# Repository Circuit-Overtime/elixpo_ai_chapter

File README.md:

<div align="center">

# LixBlogs

### Write, collaborate, and publish beautifully.

A modern blogging platform with a rich block editor, AI writing assistant,<br />
real-time collaboration, and organizations — all on the edge.

<br />

[Website](https://blogs.elixpo.com) ·
[Discussions](https://github.com/orgs/elixpo/discussions) ·
[Elixpo](https://elixpo.com) ·
[Chapter](https://github.com/elixpo/elixpo_chapter)

</div>

<br />

<div align="center">

</div>

<br />

## About

LixBlogs (also called **Elixpo Blogs**) is an **open-source publishing
platform** designed for creators, developers, and teams. It gives you a
beautiful writing experience with powerful tools built right in — a rich block
editor, an AI writing assistant, real-time collaboration, and organizations —
all deployed on **Cloudflare's edge** and hosted at
[blogs.elixpo.com](https://blogs.elixpo.com).

It supports personal publishing, organization publications, and collaborative
editing. Availability, account requirements, and operated-service limits are
documented by the hosted service rather than promised by this README.

This is a monorepo: alongside the platform it ships **`@elixpo/lixeditor`** (the
editor on npm) and the **LixEditor** VS Code extension. It is part of the wider
Elixpo ecosystem.

<br />

<div align="center">

| | Feature | Description |
|:---:|:---|:---|
| :sparkles: | **AI Writing Assistant** | Press `Space` on an empty line — generate text, images, and get inline suggestions |
| :jigsaw: | **Rich Block Editor** | 20+ block types — code, math equations, diagrams, embeds, tables, and more |
| :busts_in_silhouette: | **Real-Time Collaboration** | Invite co-authors and edit together with live cursors and presence |
| :office: | **Organizations & Teams** | Create orgs, assign roles, organize content into collections |
| :cloud: | **Auto-Save & Cloud Sync** | Drafts save locally and sync to the cloud — never lose a word |
| :art: | **Themes & Customization** | Light & dark modes, custom page colors, cover images, page emojis |
| :link: | **Link Previews** | Hover any link to see a rich OG preview card with title, image, favicon |
| :page_facing_up: | **Sub-Pages** | Nest pages inside your blog for structured, multi-page content |
| :framed_picture: | **Media Uploads** | Drag & drop images, auto-compressed to WebP, with platform or creator-owned Cloudinary storage |
| :bookmark_tabs: | **Library & Bookmarks** | Save posts, organize into collections, track reading history |

</div>

## Elixpo relationship

LixBlogs is an active core service of the Elixpo open-source project foundry.
Its platform, editor package, publishing CLI, and extension are developed in
this repository. The canonical directory of current Projects, Research, and
Services lives at [elixpo.com](https://elixpo.com); this README does not copy
that directory because lifecycle information changes independently.

<br />

## `@elixpo/lixeditor` — Use Our Editor Anywhere

The editor that powers LixBlogs is available as a **standalone npm package**. Drop it into any React or Next.js app to get a fully-featured WYSIWYG editor with equations, diagrams, code highlighting, and more.

```bash
npm install @elixpo/lixeditor @blocknote/core @blocknote/react @blocknote/mantine
```

```jsx
import { LixEditor, LixPreview, LixThemeProvider } from '@elixpo/lixeditor';
import '@blocknote/core/fonts/inter.css';
import '@blocknote/mantine/style.css';
import '@elixpo/lixeditor/styles';

function App() {
  const [blocks, setBlocks] = useState(null);

  return (
    <LixThemeProvider defaultTheme="dark">
      <LixEditor
        initialContent={blocks}
        onChange={(editor) => setBlocks(editor.getBlocks())}
        features={{ equations: true, mermaid: true, codeHighlighting: true }}
        placeholder="Start writing..."
      />
      <LixPreview blocks={blocks} />
    </LixThemeProvider>
  );
}
```

<div align="center">

| Feature | Default | Description |
|---------|:-------:|-------------|
| `equations` | :white_check_mark: | Block & inline LaTeX via KaTeX |
| `mermaid` | :white_check_mark: | Mermaid diagrams (flowcharts, sequence, git graphs) |
| `codeHighlighting` | :white_check_mark: | Shiki syntax highlighting — 30+ languages |
| `tableOfContents` | :white_check_mark: | Auto-generated TOC from headings |
| `images` | :white_check_mark: | Upload, embed URL, paste, drag & drop |
| `dates` | :white_check_mark: | Inline date picker chips |
| `linkPreview` | :white_check_mark: | OG metadata tooltip on link hover |
| `markdownLinks` | :white_check_mark: | Auto-convert `[text](url)` and `` |

</div>

Every feature is toggleable. Override CSS variables to match your brand:

```css
:root {
  --lix-accent: #e040fb;
  --lix-bg-app: #fafafa;
  --lix-font-body: 'Inter', sans-serif;
}
```

:point_right: **[Full documentation →](packages/lixeditor/README.md)**

<br />

## LixEditor for VS Code

Write `.lixeditor` documents with a rich WYSIWYG editor — right inside VS Code.

<div align="center">

</div>

| | Feature |
|:---:|:---|
| :writing_hand: | Rich block editor — headings, lists, tables, checklists |
| :art: | Syntax-highlighted code blocks (25+ languages via Shiki) |
| :link: | Smart links — auto-convert `[text](url)`, hover preview |
| :framed_picture: | Image blocks — upload, embed URL, paste, drag & drop |
| :calendar: | Date stamps — `Ctrl+D` to insert |
| :zap: | Slash commands — type `/` to insert any block |
| :floppy_disk: | Auto-save + manual save + Markdown export |
| :art: | Adapts to your VS Code theme (light/dark) |

```
1. Install the extension from the VS Code Marketplace
2. Create a file: notes.lixeditor
3. Open it — the rich editor loads automatically
4. Type / for commands, write with markdown shortcuts
```

:point_right: **[Extension docs →](packages/vscode-lixeditor/README.md)**

<br />

## How It Works

```mermaid
graph LR
    A["🔐 Sign Up"] -->|Elixpo OAuth| B["✍️ Write"]
    B -->|Block Editor| C["🤖 AI Assist"]
    C -->|Generate & Edit| D["👥 Collaborate"]
    D -->|Real-time Sync| E["🚀 Publish"]
    E -->|blogs.elixpo.com| F["🌍 Readers"]

    style A fill:#9b7bf7,stroke:#7c5ce0,color:#fff
    style B fill:#60a5fa,stroke:#3b82f6,color:#fff
    style C fill:#c084fc,stroke:#a855f7,color:#fff
    style D fill:#4ade80,stroke:#22c55e,color:#fff
    style E fill:#f59e0b,stroke:#d97706,color:#fff
    style F fill:#f87171,stroke:#ef4444,color:#fff
```

<br />

## The Editor

The heart of LixBlogs is a **powerful block editor** built on [BlockNote](https://blocknotejs.org) — it feels like writing in Notion, but built for publishing.

<div align="center">

| Block Type | What It Does |
|:---|:---|
| Paragraphs, Headings | Standard text with markdown shortcuts |
| Code Blocks | Syntax-highlighted with 30+ languages via Shiki |
| Math / LaTeX | Block & inline equations with KaTeX rendering |
| Mermaid Diagrams | Flowcharts, sequence diagrams, git graphs, and more |
| Images | Upload, embed URL, paste, drag & drop — auto WebP compression |
| Links | Auto-convert URLs, `[text](url)` syntax, OG preview on hover |
| Tables | Full table support with header rows |
| Checklists | Interactive checkboxes with checked/unchecked styling |
| Table of Contents | Auto-generated from your headings |
| Sub-Pages | Nest child pages inside your blog |
| Date Stamps | Inline date chips with a mini calendar picker |
| Mentions | Tag users `@name`, blogs, and organizations |
| Dividers | Horizontal rules to separate sections |

</div>

<br />

## Monorepo layout

```
.
├── app/                       # Next.js App Router pages, layouts, API routes
├── src/                       # React components (Editor/), views, context, AI
├── lib/                       # Server-side utilities (auth, media, tiers)
├── migrations/                # Cloudflare D1 SQL migrations
├── worker/                    # Cloudflare Worker code
├── packages/
│   ├── lixeditor/             # @elixpo/lixeditor — the editor (npm)
│   ├── vscode-lixeditor/      # elixpo.lixeditor — VS Code extension
│   └── lixsketch/             # @elixpo/lixsketch — the whiteboard editor
└── public/                    # Static assets, brand marks, fonts
```

## Architecture

```mermaid
graph TB
    subgraph Client ["🖥️ Client"]
        FE["Next.js 15 + React 19"]
        ED["@elixpo/lixeditor"]
        YJS["Yjs CRDT"]
    end

    subgraph Edge ["☁️ Cloudflare Edge"]
        CF["Pages + Workers"]
        D1["D1 Database"]
        DO["Durable Objects"]
        KV["KV Cache"]
    end

    subgraph Services ["🔌 Services"]
        AI["LixSearch AI"]
        CLD["Cloudinary"]
        AUTH["Elixpo Accounts"]
    end

    FE --> CF
    ED --> YJS
    YJS -->|WebSocket| DO
    CF --> D1
    CF --> KV
    FE --> AI
    FE --> CLD
    FE --> AUTH

    style Client fill:#1a1a2e,stroke:#9b7bf7,color:#e8edf5
    style Edge fill:#1a1a2e,stroke:#60a5fa,color:#e8edf5
    style Services fill:#1a1a2e,stroke:#4ade80,color:#e8edf5
```

<br />

## Running locally

Copy [`.env.example`](.env.example) to `.env.local` and fill in the values
before starting the app. Only the **Auth** block is needed to sign in locally;
every other section is marked optional and only affects its own feature.
It is the single source for local secrets used by both Next.js and the
Cloudflare platform proxy. Do not create `.dev.vars`; Wrangler gives that file
precedence and it can silently shadow `.env.local` with stale values.

```bash
cp .env.example .env.local
npm install
npm run dev
```

Then open [http://localhost:3000](http://localhost:3000).

Before opening a pull request, run the same checks CI runs:

```bash
npm test             # Unit tests (node --test)
npm run pages:build  # Cloudflare Pages build (@cloudflare/next-on-pages)
```

`npm run build` runs plain `next build` and does not check Cloudflare
compatibility. To preview the Cloudflare build locally, run
`npm run pages:build` first, then:

```bash
npm run db:migrate:local  # Apply D1 migrations to the local database
npm run preview           # Serve .vercel/output/static with wrangler pages dev
```

`npm run deploy` and `npm run db:migrate` act on the production Cloudflare
project and the remote D1 database. Production deploys run from CI after a
pull request is merged, so contributors do not need either command.

<br />

## Built in public

Repository history and the [contributors graph](https://github.com/elixpo/blogs.elixpo/graphs/contributors)
provide the evidence for individual contributions. See
**[CONTRIBUTING.md](CONTRIBUTING.md)**, **[GOVERNANCE.md](GOVERNANCE.md)**, and
our **[Code of Conduct](CODE_OF_CONDUCT.md)** before participating.

## Get involved

- 💬 **Join the conversation** in [GitHub Discussions](https://github.com/orgs/elixpo/discussions).
- 🚀 **Build with Elixpo** through the [Chapter repository](https://github.com/elixpo/elixpo_chapter).
- 🛠️ **Contribute to LixBlogs** through this repository's [issues](https://github.com/elixpo/blogs.elixpo/issues).

## Project Activity

<div align="center">

<br />

</div>

<br />

## Brand assets

Brand-ready marks and per-service icons live under [`public/`](public/) (logos,
mascot marks, `og-image`, and the Lix\* brand fonts under
[`public/fonts/`](public/fonts/)). A browsable kit is at
**[elixpo.com/assets](https://elixpo.com/assets)**.

## Licensing and official distributions

Read [`LICENSE`](LICENSE), the repository [notice board](LICENSES/NOTICE), and
applicable third-party notices before reuse. Elixpo is separating future code,
content, hardware, and trademark policies; this repository must not be treated
as evidence that every Elixpo project uses one universal license.

Copyright permissions do not grant permission to impersonate Elixpo or present
another deployment as the official service. This repository currently ships:

- **npm package `@elixpo/lixeditor`** (from [`packages/lixeditor/`](packages/lixeditor/)) — the published package name on the npm registry is reserved to Elixpo; reuse of the source is governed by this repository's current license and notice.
- **VS Code Marketplace extension `elixpo.lixeditor`** (publisher `elixpo`, from [`packages/vscode-lixeditor/`](packages/vscode-lixeditor/)) — the Marketplace listing and the `elixpo` publisher identity are reserved to Elixpo; source reuse remains subject to this repository's current terms.
- **Hosted service `blogs.elixpo.com`** — the official LixBlogs deployment; the brand, deployment, and operational data are reserved, while source reuse is governed by this repository's current terms.

Developers can use **[`@elixpo/lixeditor`](https://www.npmjs.com/package/@elixpo/lixeditor)** (npm) and the **[LixEditor VS Code extension](https://marketplace.visualstudio.com/items?itemName=elixpo.lixeditor)** in their own projects under MIT.

<div align="center">

**Made with :purple_heart: by [Elixpo](https://github.com/elixpo)**

[Website](https://blogs.elixpo.com) · [npm Package](https://www.npmjs.com/package/@elixpo/lixeditor) · [VS Code Extension](https://marketplace.visualstudio.com/items?itemName=elixpo.lixeditor) · [Report Bug](https://github.com/elixpo/blogs.elixpo/issues) · [Request Feature](https://github.com/elixpo/blogs.elixpo/issues)

<sub>Made in the open, together. © 2023-2026 Elixpo.</sub>

</div>

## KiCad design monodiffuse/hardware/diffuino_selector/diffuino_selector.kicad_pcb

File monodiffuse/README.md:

# MonoDiffuse

MonoDiffuse is a controlled study of one-bit-weight diffusion training. The main
question is narrow: when zero-shot one-bit post-training quantization fails, how
much can be recovered by optimizing with binary weights in the forward pass?

The current study compares parameter-compatible variants of one small residual
U-Net:

- FP32 training;
- native W1A32 training from random initialization;
- zero-shot W1A32 post-training quantization (PTQ);
- FP32-initialized W1A32 quantization-aware training (QAT); and
- a W1A1 core whose boundary, normalization, time-conditioning, scaling, and
  residual operations remain floating point.

Optimization stages use the same optimizer, 12-epoch budget, diffusion schedule,
and ancestral 1,000-step sampler. Native and FP32 models receive one stage; PTQ
adds no optimization after FP32; warm QAT receives an additional 12-epoch binary
stage after FP32 pretraining. Results are repeated over training seeds 0, 1, and 2.

## Scientific contribution

The central finding is that one-bit diffusion failure is not caused solely by the
binary representation: a substantial part is caused by projecting a solution
optimized in floating point into binary weights after training. By holding the
network parameterization fixed and changing the training path, the study
separates representational limitations from post-training projection failure.

The controlled experiments show that:

- native W1A32 optimization substantially mitigates zero-shot PTQ collapse on
  MNIST, although it remains clearly behind matched FP32 training;
- mean-centering does not reduce trained latent-to-binary angular distortion and
  worsens the strongest pre-activation condition, rejecting the proposed
  centering explanation;
- the benefit of pre-activation residual ordering is conditional rather than a
  universal stability principle;
- peak classifier confidence is invalid as a generative-quality metric in this
  setting because Gaussian noise receives near-perfect confidence; and
- the small-model CIFAR-10 experiment cannot establish natural-image binary
  performance because even its FP32 control fails by a large margin.

The scientific claim is deliberately bounded: **optimization path explains a
substantial portion of one-bit PTQ failure in this controlled MNIST setting, but
the study does not establish FP32 parity or a general teacher-free solution to
binary diffusion.** Physical bit packing, three-seed artifacts, controls, hashes,
and exact commands support this claim as reproducibility contributions rather
than being presented as a new binary-training algorithm.

## Preprint and citation

The manuscript is released as **MonoDiffuse Technical Report 2026-01** and is a
preprint that has not undergone peer review. Publication metadata, Zenodo
records, software-release fields, and the deterministic packaging command are
in [`publication/`](publication/README.md).

Build the local upload bundles with:

```bash
python scripts/package_publication.py
```

The archived preprint has the version-specific DOI
<https://doi.org/10.5281/zenodo.23424654>. The concept DOI
<https://doi.org/10.5281/zenodo.23424653> resolves to the latest version. Cite
the version-specific DOI for the reported results; [`CITATION.cff`](CITATION.cff)
contains the corresponding citation metadata. The software release is archived
separately so that paper and software citations remain distinct.

The Scholar-readable manuscript landing page is
<https://research.elixpo.com/monodiffuse/>. It mirrors the canonical preprint and
does not represent peer review or a separate publication.

## Current finding

On MNIST, the best native W1A32 condition substantially outperforms zero-shot PTQ,
but it does **not** match the FP32 baseline. Domain-feature Fréchet distance is
`46.33 ± 17.24` for native uncentered/pre-activation W1A32, versus
`1314.20 ± 314.96` for matched PTQ and `3.15 ± 0.38` for FP32.

The experiments also reject two claims from an earlier draft:

- mean-centering does not reduce trained latent-to-binary angular error and hurts
  the strongest pre-activation condition; and
- peak classifier confidence is not a valid quality score here, because clamped
  Gaussian noise receives mean confidence `1.000`.

The full metric suite therefore reports domain-feature Fréchet and kernel
distances, density, coverage, and class-prior Jensen--Shannon divergence, with
real--real and Gaussian-noise controls. On CIFAR-10, W1A1-core has the best mean
domain-feature Fréchet distance among the tested models (`365.02 ± 26.97`), but
the FP32 baseline is also poor (`382.67 ± 46.91`) relative to the real--real
control (`7.13`). Its apparent ranking is therefore not evidence of binary
natural-image success. CIFAR-10 is reported as an inconclusive, failed-model
stress test rather than a competitive benchmark.

## Reproduce the study

Install the pinned environment:

```bash
python -m venv venv
venv/bin/pip install -r requirements.txt
```

Run the tests:

```bash
venv/bin/python -m pytest -q
```

Train all MNIST conditions with three independent seeds:

```bash
venv/bin/python -m experiments.v1_binary_study.train suite \
  --dataset mnist --seeds 0,1,2 --epochs 12 \
  --batch-size 256 --base-channels 16
```

Evaluate with the exact ancestral sampler:

```bash
venv/bin/python -m experiments.v1_binary_study.evaluate suite \
  --dataset mnist --encoder-epochs 10 --eval-samples 2000 \
  --eval-batch-size 256 --sampler ddpm
```

Completed evaluations can be resumed safely with `--resume`. The committed
aggregate tables are in `artifacts/v1_binary_study/{mnist,cifar10}/summary.json`.

Export physically packed binary inference weights:

```bash
venv/bin/python -m experiments.v1_binary_study.export \
  artifacts/v1_binary_study/mnist/native_uncentered_pre/seed_0/checkpoint.pt
```

The representative packed tensor payload is 121,316 bytes, versus 875,972 bytes
for the FP32 state (7.22×). This is a storage measurement. The project does not yet
implement packed XNOR convolution kernels and makes no measured latency or energy
claim.

## Diffuino hardware artifact

Diffuino runs live class-conditioned MNIST denoising on the Arduino UNO Q's
Qualcomm processor and streams frames to the STM32-driven 8×13 LED matrix. This
is a separate system demonstration: its reliable interactive default is FP32 and
is not evidence for the controlled binary-model results. The paper-linked W1A32
model is also exportable to ONNX, but its binary-trained weights execute as
ordinary floating-point convolution tensors rather than packed XNOR operations.

Build the installable Arduino App archive with:

~~~bash
python -m apps.diffuino.package_app
~~~

The resulting dist/diffuino.zip can be copied to an UNO Q and installed with
arduino-app-cli app import ~/diffuino.zip. Full flash, CLI, status-LED, and model
details are in [apps/diffuino/README.md](apps/diffuino/README.md).
The reproducible BCD-selector circuit, KiCad source, zero-warning ERC report,
bill of materials, and exhaustive truth table are in
[hardware/diffuino_selector](hardware/diffuino_selector/README.md).

## Repository map

- `experiments/v1_binary_study/`: matched models, training, evaluation, export,
  tests, and exact commands;
- `artifacts/v1_binary_study/`: per-seed checkpoints, hashes, histories, metrics,
  controls, summaries, and sample grids;
- `paper/v0_mnist/`: the combined archival technical report;
- `paper/v1_mnist_narrow/`: the focused MNIST manuscript and its arXiv source;
- `hardware/diffuino_selector/`: KiCad source and publication exports for the
  BCD input, validity gate, generate trigger, and reset circuit;
- `experiments/v0_mnist/`: archived exploratory scripts and figures, not the
  source of the controlled-study results.

Build the focused manuscript from `paper/v1_mnist_narrow` with `latexmk -pdf
paper.tex`. Afterward, create a self-contained arXiv upload archive with:

~~~bash
python3 scripts/package_narrow_arxiv.py
~~~

## License

[MIT](LICENSE)

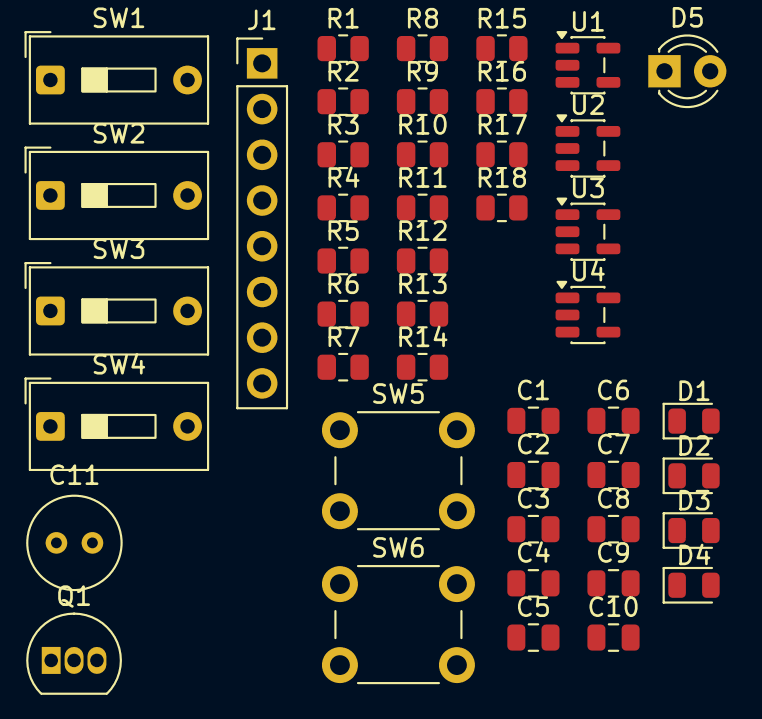
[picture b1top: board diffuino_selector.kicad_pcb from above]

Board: 2 copper layers, 46 parts (0 on the bottom side), 24 nets, no tracks yet.

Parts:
C1, C2, C3, C4: 10nF; C_0805_2012Metric
C5, C6, C7, C8, C9, C10: 100nF; C_0805_2012Metric
C11: 10uF; C_Radial_D5.0mm_H5.0mm_P2.00mm
D1: BCD3; LED_0805_2012Metric
D2: BCD2; LED_0805_2012Metric
D3: BCD1; LED_0805_2012Metric
D4: BCD0; LED_0805_2012Metric
D5: GREEN; LED_D3.0mm
J1: ARDUINO_UNO_Q; PinHeader_1x08_P2.54mm_Vertical
Q1: 2N3904; TO-92_Inline
R1, R2, R3, R4, R13, R15, R17: 10k; R_0805_2012Metric
R5, R6, R7, R8, R9, R10, R11, R12, R14, R16, R18: 1k; R_0805_2012Metric
SW1: BCD3; SW_DIP_SPSTx01_Slide_9.78x4.72mm_W7.62mm_P2.54mm
SW2: BCD2; SW_DIP_SPSTx01_Slide_9.78x4.72mm_W7.62mm_P2.54mm
SW3: BCD1; SW_DIP_SPSTx01_Slide_9.78x4.72mm_W7.62mm_P2.54mm
SW4: BCD0; SW_DIP_SPSTx01_Slide_9.78x4.72mm_W7.62mm_P2.54mm
SW5: GENERATE; SW_PUSH_6mm
SW6: RESET; SW_PUSH_6mm
U1: 74AHC1G32; SOT-23-5
U2, U4: 74AHC1G08; SOT-23-5
U3: 74AHC1G04; SOT-23-5

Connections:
+5V: C7.1, C8.1, C9.1, C10.1, C11.1, J1.7, R16.1, SW1.1 (A), SW2.1 (A), SW3.1 (A), SW4.1 (A), SW5.1, SW6.1, U1.5 (VCC), U2.5 (VCC), U3.5 (VCC), U4.5 (VCC)
GND: C1.2, C2.2, C3.2, C4.2, C5.2, C6.2, C7.2, C8.2, C9.2, C10.2, C11.2, D1.1 (K), D2.1 (K), D3.1 (K), D4.1 (K), J1.6, Q1.3 (E), R1.2, R2.2, R3.2, R4.2, R13.2, R17.2, U1.3 (GND), U2.3 (GND), U3.3 (GND), U4.3 (GND)
unnamed: C5.1, R13.1, SW5.2, U4.2
unnamed: C6.1, R17.1, R18.1, SW6.2
unnamed: D1.2 (A), R9.2
unnamed: D2.2 (A), R10.2
unnamed: D3.2 (A), R11.2
unnamed: D4.2 (A), R12.2
unnamed: D5.2 (A), R16.2
unnamed: D5.1 (K), Q1.2 (C)
unnamed: J1.5, R8.2
unnamed: Q1.1 (B), R15.2
unnamed: R5.2, U2.1
unnamed: R6.2, U1.2
unnamed: R7.2, U1.1
unnamed: R14.1, U4.4
unnamed: R14.2, R15.1
unnamed: C1.1, R1.1, R5.1, R9.1, SW1.2 (B)
unnamed: C2.1, R2.1, R6.1, R10.1, SW2.2 (B)
unnamed: C3.1, R3.1, R7.1, R11.1, SW3.2 (B)
unnamed: C4.1, R4.1, R8.1, R12.1, SW4.2 (B)
unnamed: U1.4, U2.2
unnamed: U2.4, U3.2
unnamed: U3.4, U4.1

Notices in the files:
README.md:
License: See repository terms
